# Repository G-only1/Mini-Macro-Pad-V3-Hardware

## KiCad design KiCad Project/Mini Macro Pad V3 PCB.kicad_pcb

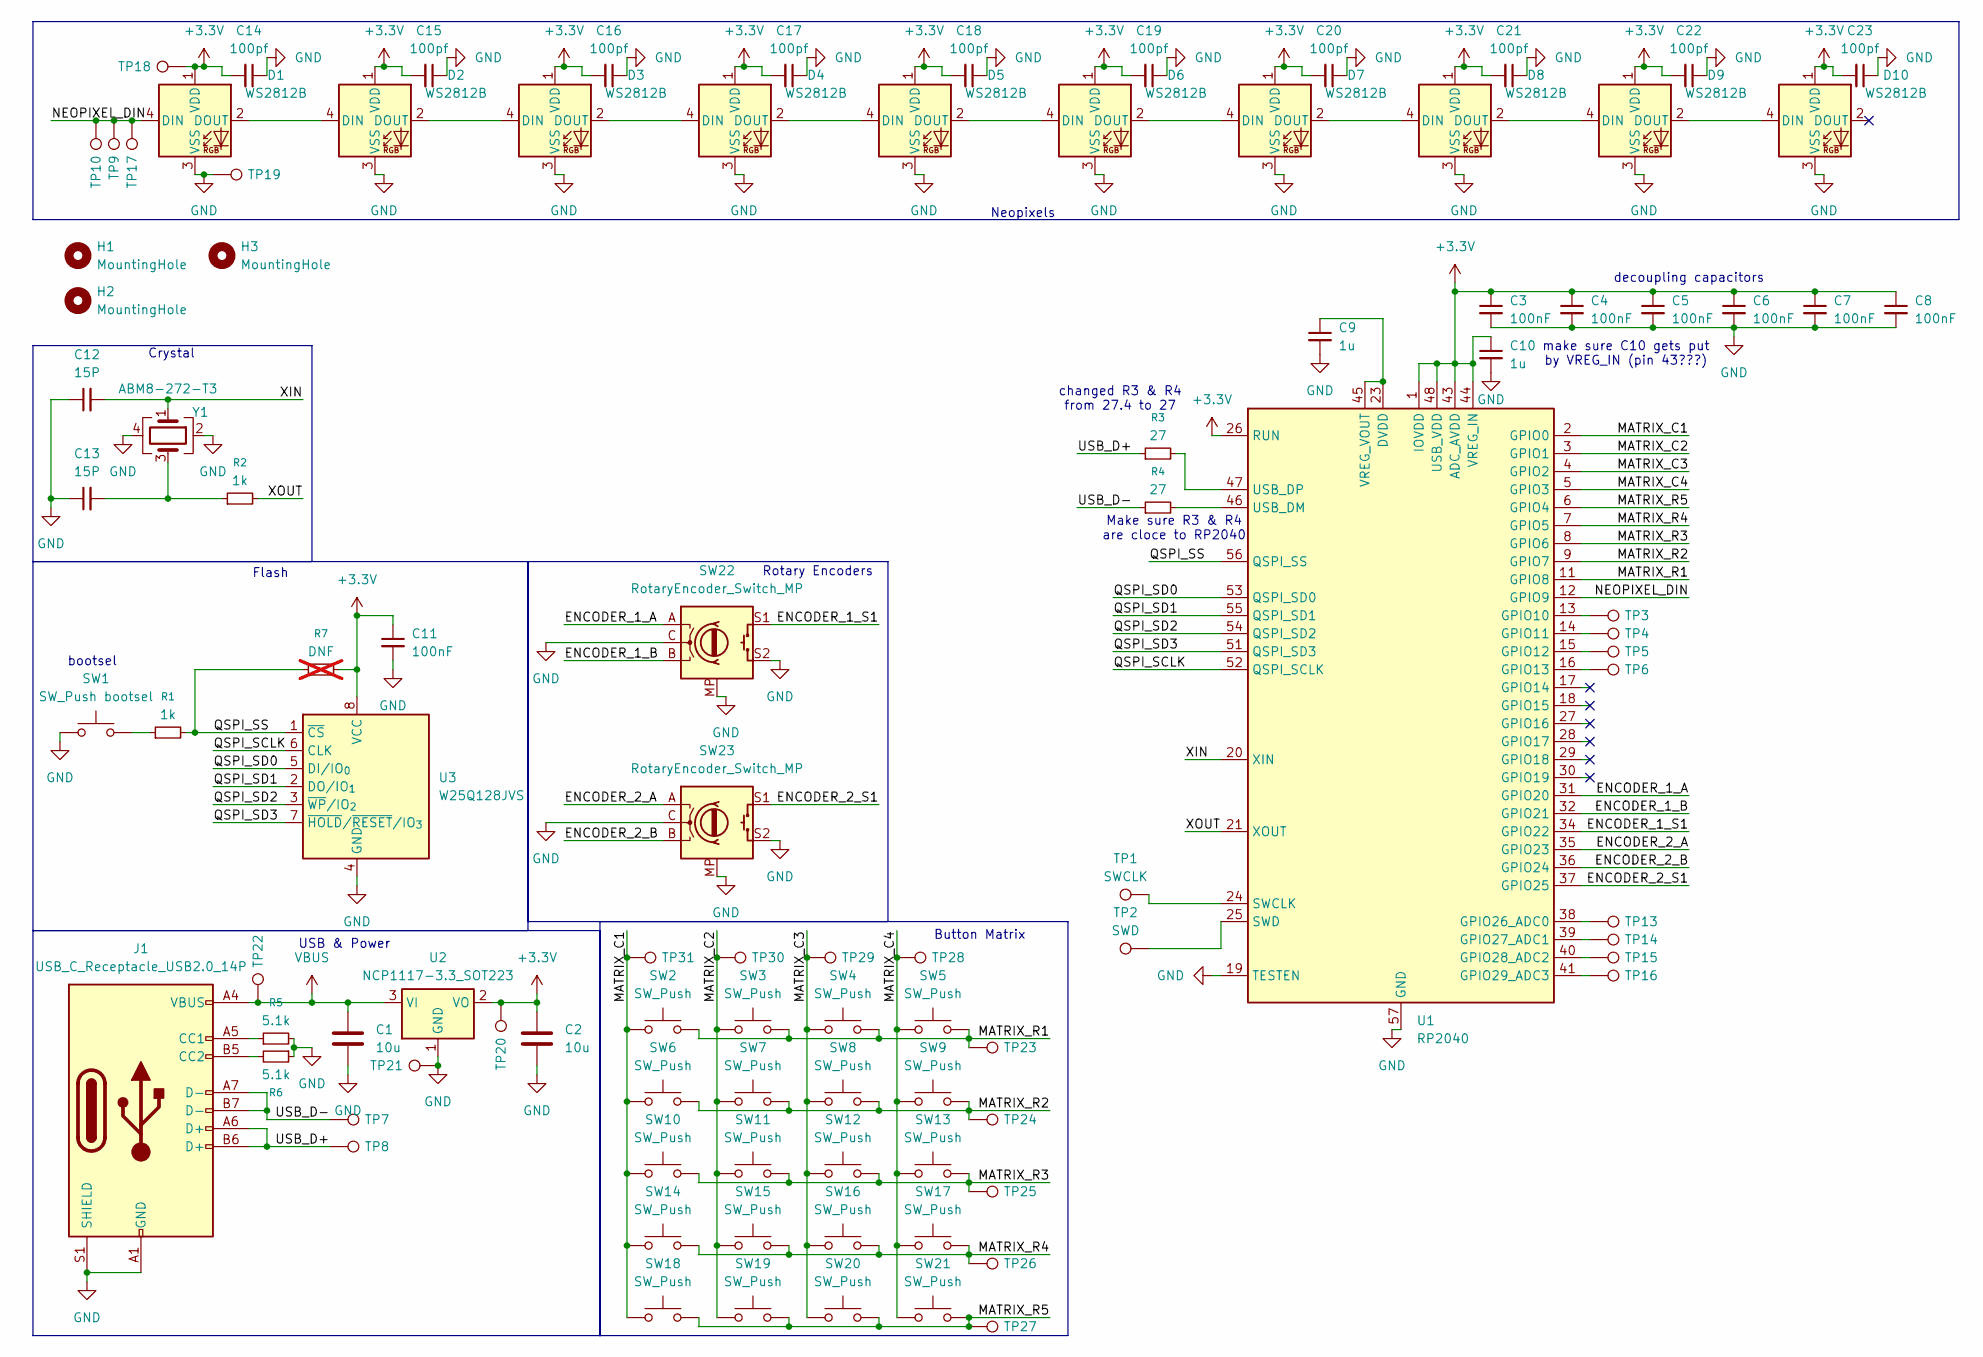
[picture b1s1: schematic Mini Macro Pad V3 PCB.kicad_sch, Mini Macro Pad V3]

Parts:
C1, C2: 10u; C_0603_1608Metric
C3, C4, C5, C6, C7, C8, C11: 100nF; C_0603_1608Metric
C9, C10: 1u; C_0603_1608Metric
C12, C13: 15P; C_0603_1608Metric
C14, C15, C16, C17, C18, C19, C20, C21, C22, C23: 100pf; C_0603_1608Metric
D1, D2, D3, D4, D5, D6, D7, D8, D9, D10: WS2812B; LED_WS2812B_PLCC4_5.0x5.0mm_P3.2mm
H1, H2, H3: MountingHole; ToolingHole_1.152mm
J1: USB_C_Receptacle_USB2.0_14P; USB_C_Receptacle_GCT_USB4105-xx-A_16P_TopMnt_Horizontal
R1, R2: 1k; R_0603_1608Metric
R3, R4: 27; R_0603_1608Metric
R5, R6: 5.1k; R_0603_1608Metric
R7: DNF; R_0402_1005Metric_Pad0.72x0.64mm_HandSolder; not fitted
SW1: SW_Push bootsel; SW_PUSH_6mm_H5mm
SW2, SW3, SW4, SW5, SW6, SW7, SW8, SW9, SW10, SW11, SW12, SW13, SW14, SW15, SW16, SW17, SW18, SW19, SW20, SW21: SW_Push; SW_PUSH_6mm_H5mm
SW22, SW23: RotaryEncoder_Switch_MP; RotaryEncoder_Bourns_Horizontal_PEC12R-2x17F-Sxxxx
TP1: SWCLK; TestPoint_Pad_1.5x1.5mm
TP2: SWD; TestPoint_Pad_1.5x1.5mm
TP3, TP4, TP5, TP6, TP7, TP8, TP9, TP10, TP13, TP14, TP15, TP16, TP17, TP18, TP19, TP20, TP21, TP22, TP23, TP24, TP25, TP26, TP27, TP28, TP29, TP30, TP31: TestPoint_Pad_1.5x1.5mm
U1: RP2040; QFN-56-1EP_7x7mm_P0.4mm_EP3.2x3.2mm_ThermalVias
U2: NCP1117-3.3_SOT223; SOT-223-3_TabPin2
U3: W25Q128JVS; SOIC-8_5.3x5.3mm_P1.27mm
Y1: ABM8-272-T3; ABM8-272-T3_ABR

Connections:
+3.3V: C2.1, C3.1, C4.1, C5.1, C6.1, C7.1, C8.1, C10.1, C11.1, C14.2, C15.2, C16.2, C17.2, C18.2, C19.2, C20.2, C21.2, C22.2, C23.2, D1.1 (VDD), D2.1 (VDD), D3.1 (VDD), D4.1 (VDD), D5.1 (VDD), D6.1 (VDD), D7.1 (VDD), D8.1 (VDD), D9.1 (VDD), D10.1 (VDD), R7.2, TP18.1, TP20.1, U1.1 (IOVDD), U1.10 (IOVDD), U1.22 (IOVDD), U1.26 (RUN), U1.33 (IOVDD), U1.42 (IOVDD), U1.43 (ADC_AVDD), U1.44 (VREG_IN), U1.48 (USB_VDD), U1.49 (IOVDD), U2.2 (VO), U3.8 (VCC)
/ENCODER_1_A: SW22.A, U1.31 (GPIO20)
/ENCODER_1_B: SW22.B, U1.32 (GPIO21)
/ENCODER_1_S1: SW22.S1, U1.34 (GPIO22)
/ENCODER_2_A: SW23.A, U1.35 (GPIO23)
/ENCODER_2_B: SW23.B, U1.36 (GPIO24)
/ENCODER_2_S1: SW23.S1, U1.37 (GPIO25)
/MATRIX_C1: SW2.1, SW6.1, SW10.1, SW14.1, SW18.1, TP31.1, U1.2 (GPIO0)
/MATRIX_C2: SW3.1, SW7.1, SW11.1, SW15.1, SW19.1, TP30.1, U1.3 (GPIO1)
/MATRIX_C3: SW4.1, SW8.1, SW12.1, SW16.1, SW20.1, TP29.1, U1.4 (GPIO2)
/MATRIX_C4: SW5.1, SW9.1, SW13.1, SW17.1, SW21.1, TP28.1, U1.5 (GPIO3)
/MATRIX_R1: SW2.2, SW3.2, SW4.2, SW5.2, TP23.1, U1.11 (GPIO8)
/MATRIX_R2: SW6.2, SW7.2, SW8.2, SW9.2, TP24.1, U1.9 (GPIO7)
/MATRIX_R3: SW10.2, SW11.2, SW12.2, SW13.2, TP25.1, U1.8 (GPIO6)
/MATRIX_R4: SW14.2, SW15.2, SW16.2, SW17.2, TP26.1, U1.7 (GPIO5)
/MATRIX_R5: SW18.2, SW19.2, SW20.2, SW21.2, TP27.1, U1.6 (GPIO4)
/NEOPIXEL_DIN: D1.4 (DIN), TP9.1, TP10.1, TP17.1, U1.12 (GPIO9)
/QSPI_SCLK: U1.52 (QSPI_SCLK), U3.6 (CLK)
/QSPI_SD0: U1.53 (QSPI_SD0), U3.5 (DI/IO_{0})
/QSPI_SD1: U1.55 (QSPI_SD1), U3.2 (DO/IO_{1})
/QSPI_SD2: U1.54 (QSPI_SD2), U3.3 (~WP/IO_{2})
/QSPI_SD3: U1.51 (QSPI_SD3), U3.7 (~HOLD/~RESET/IO_{3})
/QSPI_SS: R1.2, R7.1, U1.56 (QSPI_SS), U3.1 (~CS)
/USB_D+: J1.A6 (D+), J1.B6 (D+), R3.1, TP8.1
/USB_D-: J1.A7 (D-), J1.B7 (D-), R4.1, TP7.1
/XIN: C12.2, U1.20 (XIN), Y1.1
/XOUT: R2.2, U1.21 (XOUT)
GND: C1.2, C2.2, C3.2, C4.2, C5.2, C6.2, C7.2, C8.2, C9.2, C10.2, C11.2, C12.1, C13.1, C14.1, C15.1, C16.1, C17.1, C18.1, C19.1, C20.1, C21.1, C22.1, C23.1, D1.3 (VSS), D2.3 (VSS), D3.3 (VSS), D4.3 (VSS), D5.3 (VSS), D6.3 (VSS), D7.3 (VSS), D8.3 (VSS), D9.3 (VSS), D10.3 (VSS), J1.A1 (GND), J1.A12 (GND), J1.B1 (GND), J1.B12 (GND), J1.S1 (SHIELD), R5.2, R6.1, SW1.1, SW22.C, SW22.MP, SW22.S2, SW23.C, SW23.MP, SW23.S2, TP19.1, TP21.1, U1.19 (TESTEN), U1.57 (GND), U2.1 (GND), U3.4 (GND), Y1.2, Y1.4
unnamed: C13.2, R2.1, Y1.3
unnamed: D1.2 (DOUT), D2.4 (DIN)
unnamed: D2.2 (DOUT), D3.4 (DIN)
unnamed: D3.2 (DOUT), D4.4 (DIN)
unnamed: D4.2 (DOUT), D5.4 (DIN)
unnamed: D5.2 (DOUT), D6.4 (DIN)
unnamed: D6.2 (DOUT), D7.4 (DIN)
unnamed: D7.2 (DOUT), D8.4 (DIN)
unnamed: D8.2 (DOUT), D9.4 (DIN)
unnamed: D9.2 (DOUT), D10.4 (DIN)
unnamed: J1.A5 (CC1), R5.1
unnamed: J1.B5 (CC2), R6.2
unnamed: R1.1, SW1.2
unnamed: TP3.1, U1.13 (GPIO10)
unnamed: TP4.1, U1.14 (GPIO11)
unnamed: TP5.1, U1.15 (GPIO12)
unnamed: TP6.1, U1.16 (GPIO13)
unnamed: TP13.1, U1.38 (GPIO26_ADC0)
unnamed: TP14.1, U1.39 (GPIO27_ADC1)
unnamed: TP15.1, U1.40 (GPIO28_ADC2)
unnamed: TP16.1, U1.41 (GPIO29_ADC3)
unnamed: TP1.1, U1.24 (SWCLK)
unnamed: TP2.1, U1.25 (SWD)
unnamed: R4.2, U1.46 (USB_DM)
unnamed: R3.2, U1.47 (USB_DP)
unnamed: C9.1, U1.23 (DVDD), U1.45 (VREG_VOUT), U1.50 (DVDD)
VBUS: C1.1, J1.A4 (VBUS), J1.A9 (VBUS), J1.B4 (VBUS), J1.B9 (VBUS), TP22.1, U2.3 (VI)

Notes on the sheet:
bootsel
Flash
USB & Power
Button Matrix
Crystal
Make sure R3 & R4 are cloce to RP2040
Rotary Encoders
make sure C10 gets put by VREG_IN (pin 43???)
decoupling capacitors
Neopixels
changed R3 & R4 from 27.4 to 27

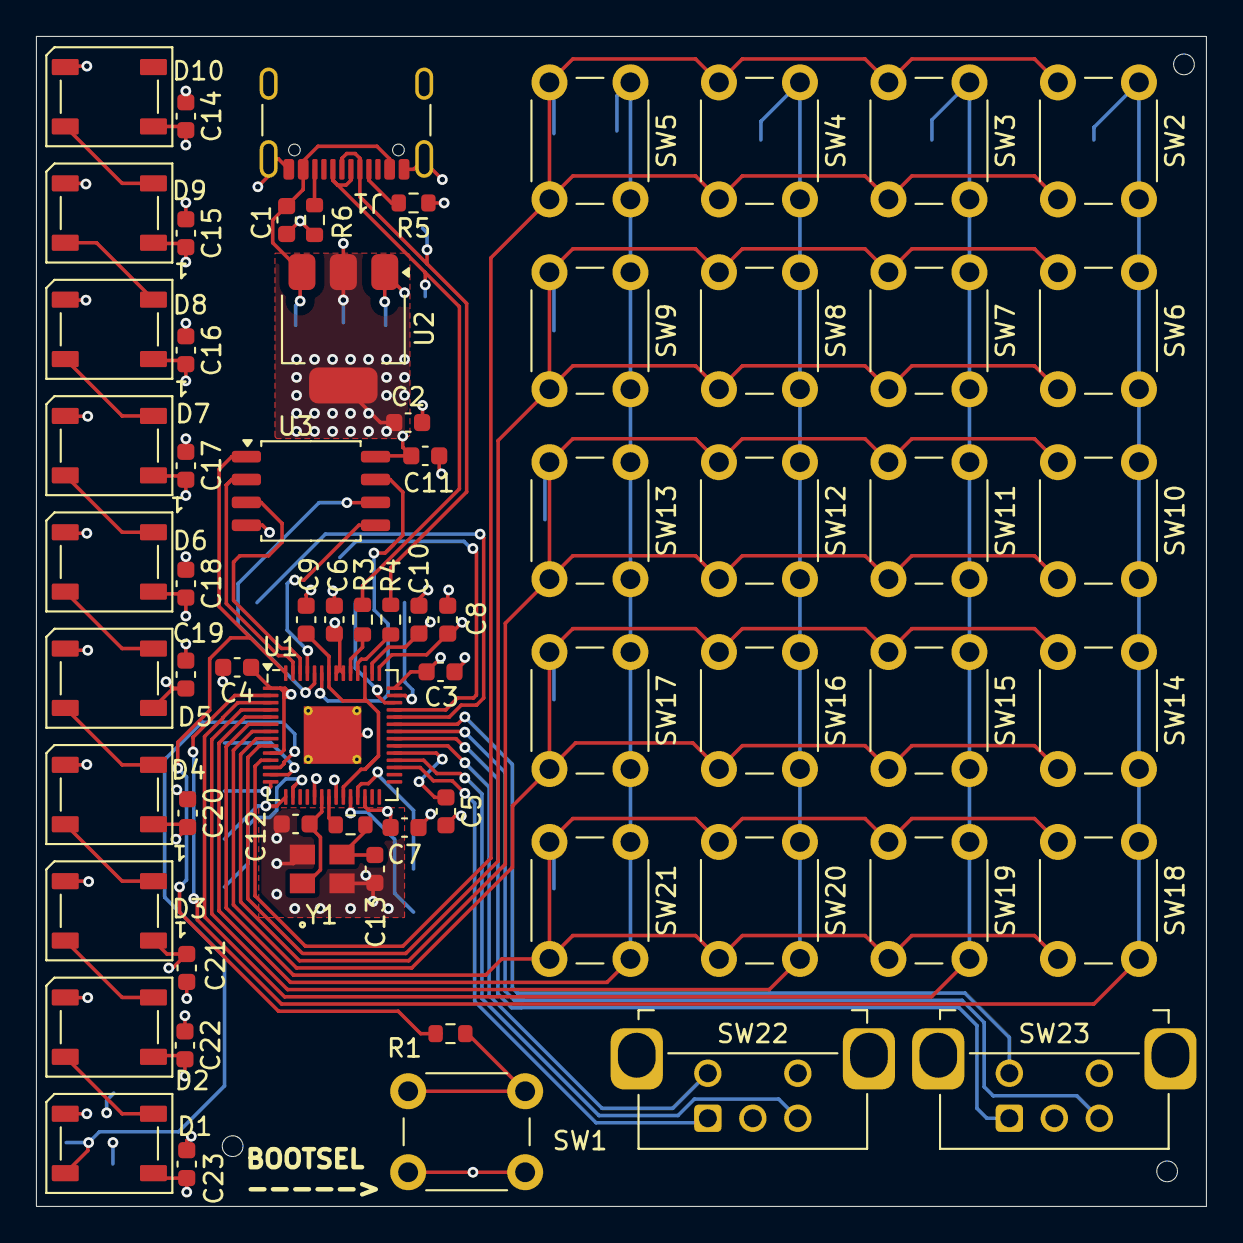
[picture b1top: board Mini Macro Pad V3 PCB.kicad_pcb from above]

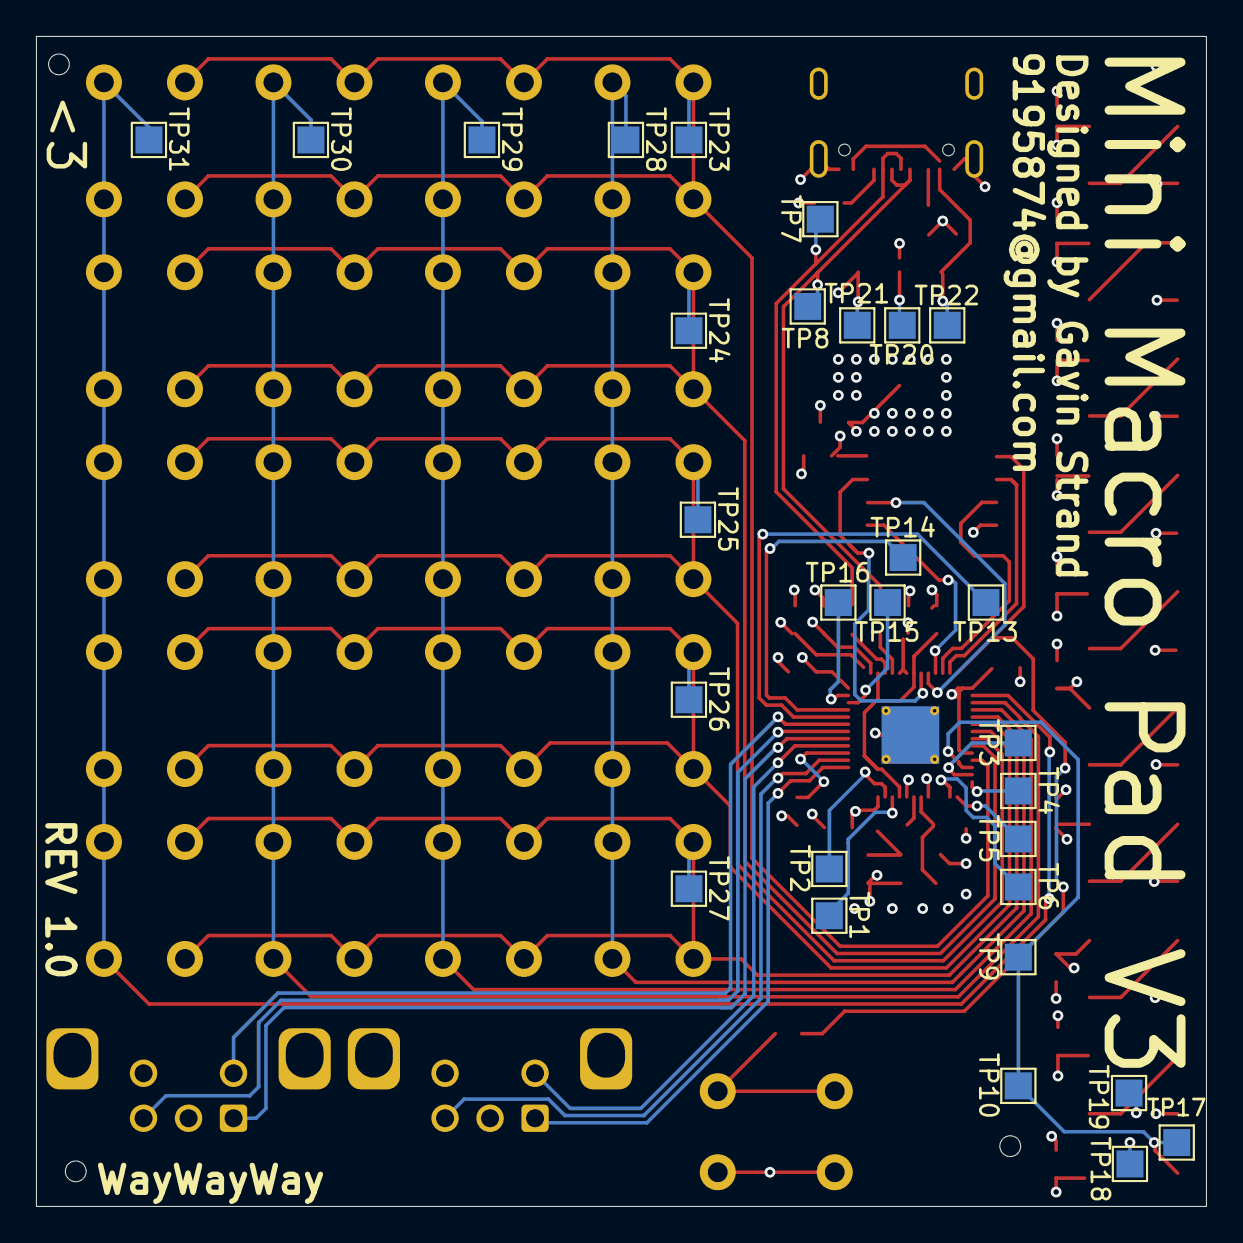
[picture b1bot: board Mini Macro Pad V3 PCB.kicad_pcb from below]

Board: 4 copper layers, 65.0 x 65.0 mm, 99 parts (29 on the bottom side), 55 nets.

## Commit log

2025-07-19 Created kicad project
2025-07-19 moved kicad project to its own folder.
2025-07-19 added basic components & neopixels to schematic
    just adding base components to schematic. not really any wiring yet
2025-07-19 added details to title block & added power supply
    power supply copied from page 7 of the raspberry pi hardware design guide for the rp2040 https://datasheets.raspberrypi.com/rp2040/hardware-design-with-rp2040.pdf
2025-07-19 same thing as previous commit
    https://datasheets.raspberrypi.com/rp2040/hardware-design-with-rp2040.pdf
2025-07-19 added flash to schematic
2025-07-19 added crystal to schematic
2025-07-19 added footprint for crystal
2025-07-19 added button matrix
    button matrix columns are connected to GPIO 0 to GPIO 3 rows are connected to GPIO 4 to GPIO 8
2025-07-19 added rotary encoders
    connected to GPIO 10 to GPIO 15
2025-07-19 assigned footprints to neopixels
2025-07-19 added to usb power
    added 5.1k resistors to CC1 & CC2
2025-07-19 Assigned footprints to all components
2025-07-19 created PCB & did rough layout
2025-07-19 more rough layout
2025-07-20 added test points & fixed layout issues with buttons
    some buttons were numbered in the wrong order.
2025-07-20 changed GPIO pins used
    moved rotary encoder GPIO pins away from the pins used for the crystal to prevent stability issues
2025-07-20 added decoupling capacitors for neopixels
2025-07-20 Started drawing traces
2025-07-20 changed some GPIO connections & did more trace routing
    Reversed the order that C1 to C5 connect in
2025-07-21 more routing traces.
2025-07-21 added ground and power planes
2025-07-21 added vias to connect components to ground & power planes
2025-07-21 more routing work
2025-07-21 test
2025-07-21 tweaks for DRC
2025-07-21 added silkscreen things
2025-07-21 moved USB C port to the right more
2025-07-21 small tweaks before ordering first prototype
2025-07-22 changed capacitor & resistor sizes
    changed sizes from 0402 to 0603 & replaced BOOTSEL button with the same kind as all the others
2025-07-22 small tweaks before ordering
2025-07-23 Changed USB C footprint
    changed because of part availability.
2025-07-23 final save before first prototype order
2025-07-25 created folder for case files
    created a new folder for the case cad files & exported a step file of the REV 1.0 PCB
2025-07-26 some case base design
2025-07-26 removed holes smaller than .2mm
2025-07-26 Replaced all micro vias with through vias
2025-11-12 fixed issue with C9 & C10 in schematic
    C9 and C10 were connected in series with a line when they should've been connected in parallel between the line and ground
2025-11-12 changed PCB to reflect changes in schematic
2026-03-12 fixes
